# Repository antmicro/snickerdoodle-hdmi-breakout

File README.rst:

===========================
Snickerdoodle HDMI breakout
===========================

Copyright (c) 2020 Antmicro <`www.antmicro.com <https://www.antmicro.com>`_>

.. figure:: img/hdmi-expansion.jpg

This repository contains open hardware design files for an expansion board compatible with `krtkl's breakyBreaky carrier board <https://www.xilinx.com/products/boards-and-kits/1-gex6t6.html>`_ for the `snickerdoodle <https://krtkl.com/snickerdoodle/>`_ prototyping platform.

The design files were created in KiCad.

The expansion board breaks out the HDMI interface on a regular HDMI connector.
The TMDS data lanes from this connector are connected to the FPGA fabric in the Zynq 7000 on the snickerdoodle module.
The expansion board should be connected to the ``JB2`` pinhead available on the breakyBreaky board. It is compatible with breakyBreaky rev.3.0 and rev.4.0 (make sure pin 1 indicators align).

Dimensions and layout
=====================

The image below shows the HDMI Expansion board's dimensions and layout.

.. figure:: img/layout.png

For more information regarding electrical connections please refer to the schematic sheets and compare them against the `offcial documentation <https://github.com/krtkl/open-source-schematics>`_ of breakyBreaky and snickerdoodle module.

License
=======

`Apache-2.0 <LICENSE>`_

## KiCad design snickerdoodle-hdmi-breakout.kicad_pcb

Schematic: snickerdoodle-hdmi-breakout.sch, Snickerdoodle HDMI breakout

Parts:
3V3, 5V0: KP-1608CGCK; LED_0603; MPN KP-1608CGCK
C1, C2, C3: C_100n_0402_6V3; 0402-cap; MPN 0402X104K6R3CT
C4: C_22u_0805; 0805-cap; MPN MC0805X226M6R3CT
C5: C_10n_0402; 0402-cap; MPN 04025G103ZAT2A
C6, C7, C8: C_22u_0805_10V; 0805-cap; MPN 0805ZD226MAT2A
D1: 1N4148WS; SOD-323F; MPN 1N4148WS
FB1: BLM18PG121SN1D; 0603-res; MPN BLM18PG121SN1D
J1: SMH-120-02-T-D; MPN SMH-120-02-T-D
J2: 685119134923; HDMI_A_Female_685119134923; MPN 685119134923
J3: solder_jumper; SolderJumper-0.6x1.4mm; MPN None
L1: XFL4020-102MEB; MPN XFL4020-102MEB
LED1, LED2: KP-1608CGCK; LED_0603; MPN KP-1608CGCK
N1: oshw_logo; oshw-logo
N2: antmicro_logo; antmicro-logo_scaled_20mm
Q1, Q2, Q3: BSS138AKA; SOT-23-3; MPN BSS138AKA
R1, R2, R4: R_10k_0402; 0402-res; MPN CRCW040210K0FKEDHP
R3, R10, R13, R14: R_0R_0402; 0402-res; MPN ERJ2GE0R00X
R5: R_470R_0402; 0402-res; MPN CRCW0402470RFKED.
R6, R7, R8: R_330R_0402; 0402-res; MPN MCMR04X3300FTL
R9: R_1M_0603; 0603-res; MPN CR0603-JW-105GLF
R11: R_100k_0402; 0402-res; MPN CRCW0402100KFKEDHP
R12: R_0R_0603; 0603-res; MPN CR0603-J/-000ELF
TP1, TP2, TP3, TP4, TP5, TP6: TP_SMD1MM; Testpoint_smd_1mm
U1: TPD12S016PWR; MPN TPD12S016PWR
U2: TPS61232DRCT; VSON-10-1EP_3x3mm; MPN TPS61232DRCT

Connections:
3V3: 3V3.1, C2.2, C4.1, J1.1, J3.2, L1.1, LED1.1, LED2.1, R2.2, U1.5 (LS_OE), U1.12 (CT_HPD), U1.24 (VCCA), U2.9 (EN), U2.10 (VIN)
5V0: 5V0.1, C1.2, R12.1, U1.11 (VCC5V)
/GP_LED1: J1.5, Q2.1 (G)
/GP_LED2: J1.7, Q3.1 (G)
/HDMI_CEC_3V3: R4.1, U1.1 (CEC_A)
/HDMI_CEC_5V: J2.13, U1.7 (CEC_B)
/HDMI_HPD_3V3: Q1.1 (G), R1.2, R3.1, U1.4 (HPD_A)
/HDMI_HPD_5V: J2.19, U1.10 (HPD_B)
/HDMI_PWR_5V: C3.2, D1.A, U1.13 (5V_OUT)
/HDMI_SCL_3V3: J1.30, R14.1, TP5.1
/HDMI_SCL_5V: J2.15, U1.8 (SCL_B)
/HDMI_SDA_3V3: J1.32, R13.1, TP6.1
/HDMI_SDA_5V: J2.16, U1.9 (SDA_B)
/IO_0_34: J1.4
/IO_L13P_T2_MRCC_34: J1.38
/IO_L14N_T2_SRCC_34: J1.37
/IO_L14P_T2_SRCC_34: J1.35
/IO_L15N_T2_DQS_34: J1.25, TP2.1
/IO_L15P_T2_DQS_34: J1.23, TP1.1
/IO_L16N_T2_34: J1.31, TP4.1
/IO_L16P_T2_34: J1.29, TP3.1
/IO_L18N_T2_34: J1.24
/IO_L18P_T2_34: J1.26
/IO_L20N_T3_34: J1.13
/IO_L20P_T3_34: J1.11
/JB2_SMB_nINT: J1.2
/SMB_I2C_SCL3: J1.39
/SMB_I2C_SDA3: J1.40
/TMDS_CLK_N: J1.19, J2.12, U1.15 (CLK-)
/TMDS_CLK_P: J1.17, J2.10, U1.16 (CLK+)
/TMDS_DATA0_N: J1.18, J2.9, U1.17 (D0-)
/TMDS_DATA0_P: J1.20, J2.7, U1.18 (D0+)
/TMDS_DATA1_N: J1.12, J2.6, U1.20 (D1-)
/TMDS_DATA1_P: J1.14, J2.4, U1.21 (D1+)
/TMDS_DATA2_N: J1.6, J2.3, U1.22 (D2-)
/TMDS_DATA2_P: J1.8, J2.1, U1.23 (D2+)
/TMDS_HPD_3V3: J1.36, Q1.3 (D), R2.1, R3.2
/VCCO_34: J1.3, J3.1
Earth: FB1.1, J2.2, J2.5, J2.8, J2.11, J2.SH
GND: C1.1, C2.1, C3.1, C4.2, C5.2, C6.2, C7.2, C8.2, FB1.2, J1.9, J1.10, J1.15, J1.16, J1.21, J1.22, J1.27, J1.28, J1.33, J1.34, J2.17, Q1.2 (S), Q2.2 (S), Q3.2 (S), R1.1, R4.2, R5.2, R6.2, R11.2, U1.6 (GND), U1.14 (GND), U1.19 (GND), U2.11 (GND)
unnamed: 3V3.2, R6.1
unnamed: 5V0.2, R5.1
unnamed: C5.1, U2.6 (SS)
unnamed: C6.1, C7.1, C8.1, R9.2, R10.1, R12.2, U2.3 (VOUT), U2.4 (VOUT)
unnamed: D1.K, J2.18
unnamed: L1.2, U2.1 (SW), U2.2 (SW)
unnamed: LED1.2, R7.1
unnamed: LED2.2, R8.1
unnamed: Q2.3 (D), R7.2
unnamed: Q3.3 (D), R8.2
unnamed: R9.1, U2.5 (PG)
unnamed: R10.2, R11.1, U2.7 (FB)
unnamed: R13.2, U1.3 (SDA_A)
unnamed: R14.2, U1.2 (SCL_A)

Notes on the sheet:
IO_L24N_T3_34
IO_L24P_T3_34
IO_L19N_T3_VREF_34
IO_L19P_T3_34
IO_L22N_T3_34
IO_L22P_T3_34
IO_L17N_T2_34
IO_L17P_T2_34
IO_L13N_T2_MRCC_34
IO_L23P_T3_34
IO_L23N_T3_34
Board-to-board connector
3V3 to 5V0 step-up converter
HDMI companion chip
P16
P15
R17
R16
W19
W18
Y19
Y18
P19
P18
N17
Optional bypass of HPD which will not invert logic state at this signal
General purpose LEDs driven from FPGA
Power indicators
Provides 5V0 system voltage for HDMI interfacing
max 2A
This connector matches the JB2 pinhead on breakyBreaky
HDMI connector
IO_L21P_T3_DQS_34
IO_L21N_T3_DQS_34
V17
V18
LEDs
HPD negation
T20
U20

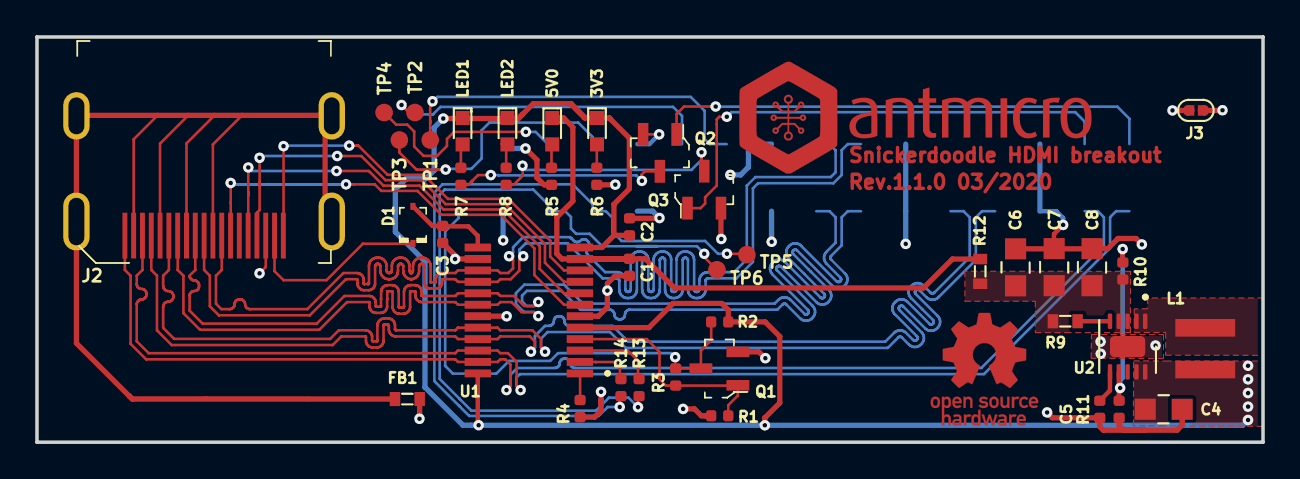
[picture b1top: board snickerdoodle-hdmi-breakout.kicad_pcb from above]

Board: 4 copper layers, 69.6 x 23.0 mm, 45 parts (1 on the bottom side), 43 nets.

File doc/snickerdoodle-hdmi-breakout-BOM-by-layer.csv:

Reference,Quantity,Value,Footprint,Manufacturer,MPN,Layer,
3V3 5V0 LED1 LED2,4,KP-1608CGCK,LED_0603,KINGBRIGHT,KP-1608CGCK,Top,
C1 C2 C3,3,C_100n_0402_6V3,0402-cap,Walsin,0402X104K6R3CT,Top,
C4,1,C_22u_0805,0805-cap,MULTICOMP,MC0805X226M6R3CT,Top,
C5,1,C_10n_0402,0402-cap,AVX,04025G103ZAT2A,Top,
C6 C7 C8,3,C_22u_0805_10V,0805-cap,AVX,0805ZD226MAT2A,Top,
D1,1,1N4148WS,SOD-323F,ON Semiconductor,1N4148WS,Top,
FB1,1,BLM18PG121SN1D,0603,Murata Electronics North America,BLM18PG121SN1D,Top,
J2,1,685119134923,HDMI_A_Female_685119134923,Amphenol,685119134923,Top,
L1,1,XFL4020-102MEB,XFL4020-102MEB,Coilcraft,XFL4020-102MEB,Top,
Q2 Q3,2,BSS138AKA,SOT-23-3,ON Semiconductor,BSS138AKA,Top,
R10 R13 R14 R3,4,R_0R_0402,0402-res,PANASONIC,ERJ2GE0R00X,Top,
R11,1,R_100k_0402,0402-res,VISHAY,CRCW0402100KFKEDHP,Top,
R12,1,R_0R_0603,0603-res,BOURNS,CR0603-J/-000ELF,Top,
R4,1,R_10k_0402,0402-res,VISHAY,CRCW040210K0FKEDHP,Top,
R5,1,R_470R_0402,0402-res,VISHAY,CRCW0402470RFKED.,Top,
R6 R7 R8,3,R_330R_0402,0402-res,MULTICOMP,MCMR04X3300FTL,Top,
R9,1,R_1M_0603,0603-res,BOURNS,CR0603-JW-105GLF,Top,
U1,1,TPD12S016PWR,TPD12S016PWR,Texas Instruments,TPD12S016PWR,Top,
U2,1,TPS61232DRCT,VSON-10-1EP_3x3mm,Texas Instruments,TPS61232DRCT,Top,
J1,1,SMH-120-02-T-D,SMH-120-02-T-D,SAMTEC,SMH-120-02-T-D,Bottom,
Q1,1,BSS138AKA,SOT-23-3,ON Semiconductor,BSS138AKA,DNP,
R1 R2,2,R_10k_0402,0402-res,VISHAY,CRCW040210K0FKEDHP,DNP,
J3,1,solder_jumper,SolderJumper-0.6x1.4mm,None,None,Virtual,
N1,1,oshw_logo,oshw-logo,,,Virtual,
N2,1,antmicro_logo,antmicro-logo,,,Virtual,
TP1 TP2 TP3 TP4 TP5 TP6,6,TP_SMD1MM,Testpoint_smd_1mm,,,Virtual,

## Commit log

2020-03-18 Added project files, added dxf outline to PCB, initial work on schematics
2020-03-18 Finished schematics, added components to PCB
2020-03-18 Defined component placement and board stackup
2020-03-18 Changed CLK connection on 40-pin connector
2020-03-18 Resolved TODOs, cleaned up the schematic layout
2020-03-18 Fixed symbol for J2 on schematics
2020-03-18 Added TODOs and some remarks
2020-03-18 Schematic cleanup
2020-03-18 Added logotypes
2020-03-18 Updated documentation, added README and LICENSE
2020-03-18 DRC resolved
2020-03-18 PCB routed with matched length of diff-pairs
2020-03-18 Updated naming convention
2020-03-18 Finished routing, minor footprint fixes
2020-03-18 Added testpads, 0R on EDID and board branding to PCB
2020-03-18 Updated component library
2020-03-18 Release 1.0.1
2020-03-18 Added BOM files
2020-03-18 Updated Manufacturer for HDMI connector
2020-03-18 README fix
2020-03-19 Added info about breakyBreaky revision 3.0 compatibility to README
2020-03-24 Prepared files for revision 1.1.0 - rotated HDMI connector, changed PCB size
2020-03-24 Added documentation for release 1.1.0
2020-03-26 Changed R10, re-generated documentation
2020-03-30 Review the README
2021-05-04 README: add photo
2021-05-04 README: update formatting, update LICENSE
2021-06-24 Notes added by 'git notes add'
